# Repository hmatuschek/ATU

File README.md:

# Simple and Portable QRP Automatic Antenna Tuner
This is a first prototype for a QRP automatic antenna tuner. The final revision should provide

  - [x] Small form factor. The chassis is already set: It should fit nicely into a 10 x 10 x 3cm
        Fischer chassis.
  - [x] Tune a random wire of 10m-ish length + 1:9 UnUn on all Bands from 80m to 10m.
  - [ ] Battery powered. The chassis should contain a rechargeable battery including its charging
        circuit.
  - [ ] Using bi-stable relays the tuner should only consume power during the actual tuning.
        This increases the battery live extensively.

## Revision 0
The first prototype lacks the battery and bistable relays. Hence, it is just a platform to develop
and optimize the firmware.

## License
(c) 2020, Hannes Matuschek, DM3MAT, dm3mat (at) darc (dot) de

The firmware and hardware are published under Creative Commons License SA-BY 4.0. See LICENSE
file for details.

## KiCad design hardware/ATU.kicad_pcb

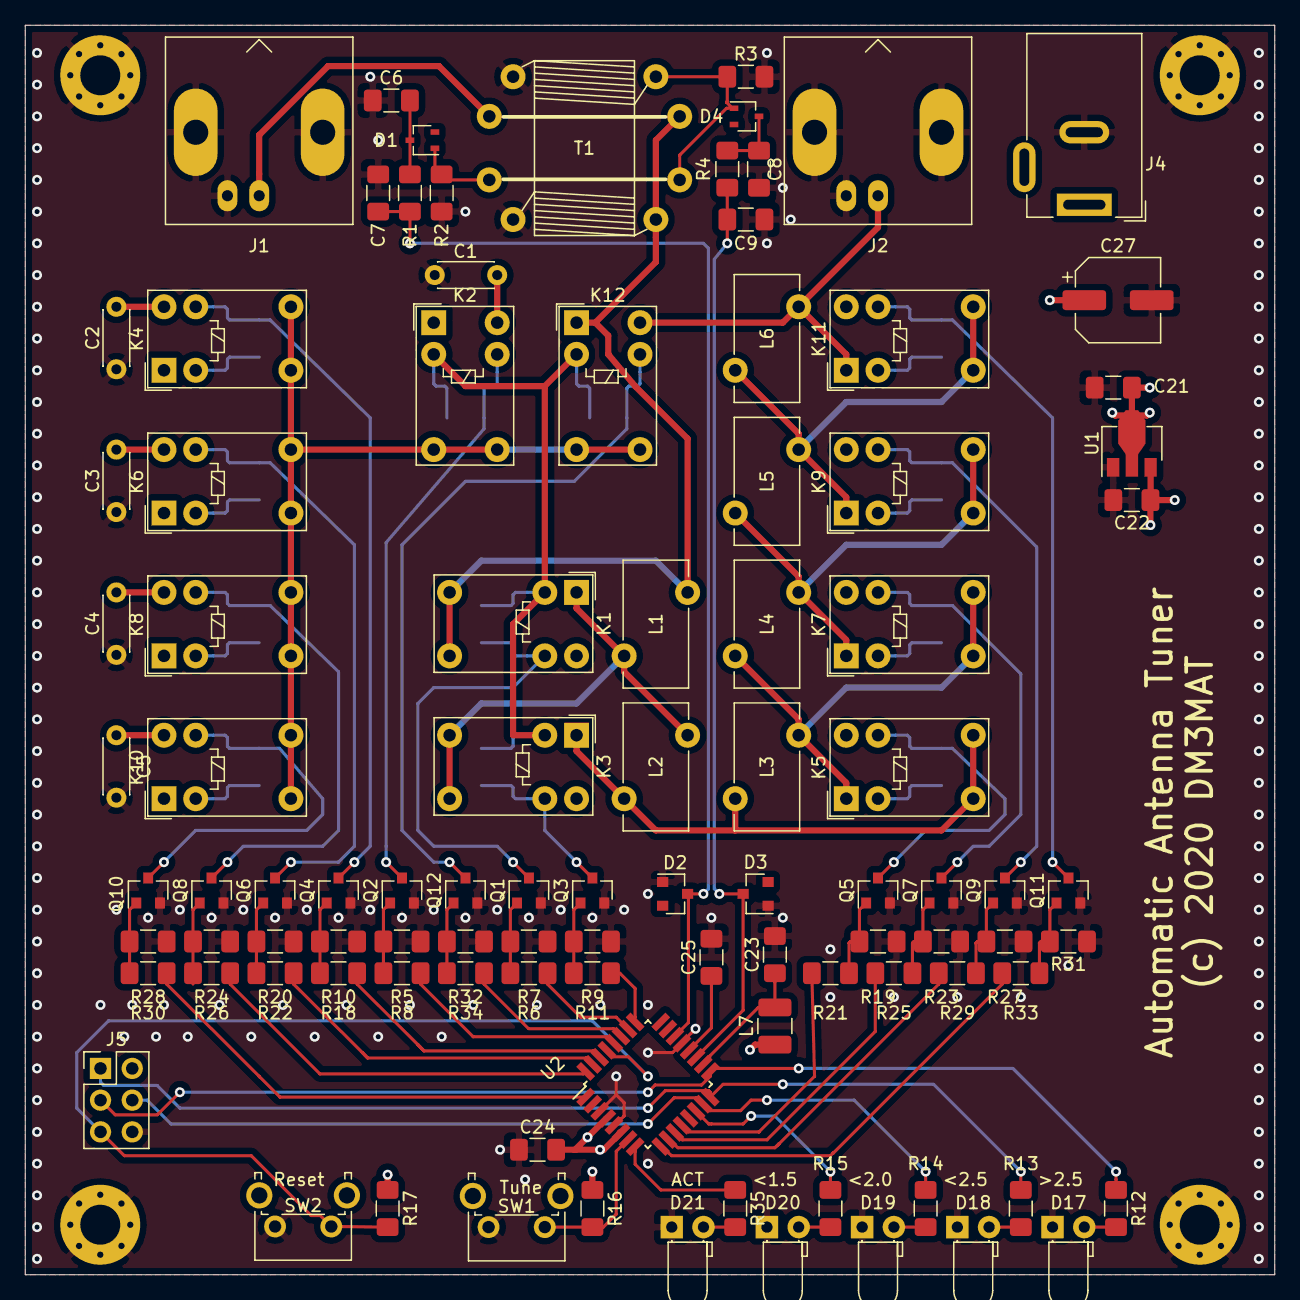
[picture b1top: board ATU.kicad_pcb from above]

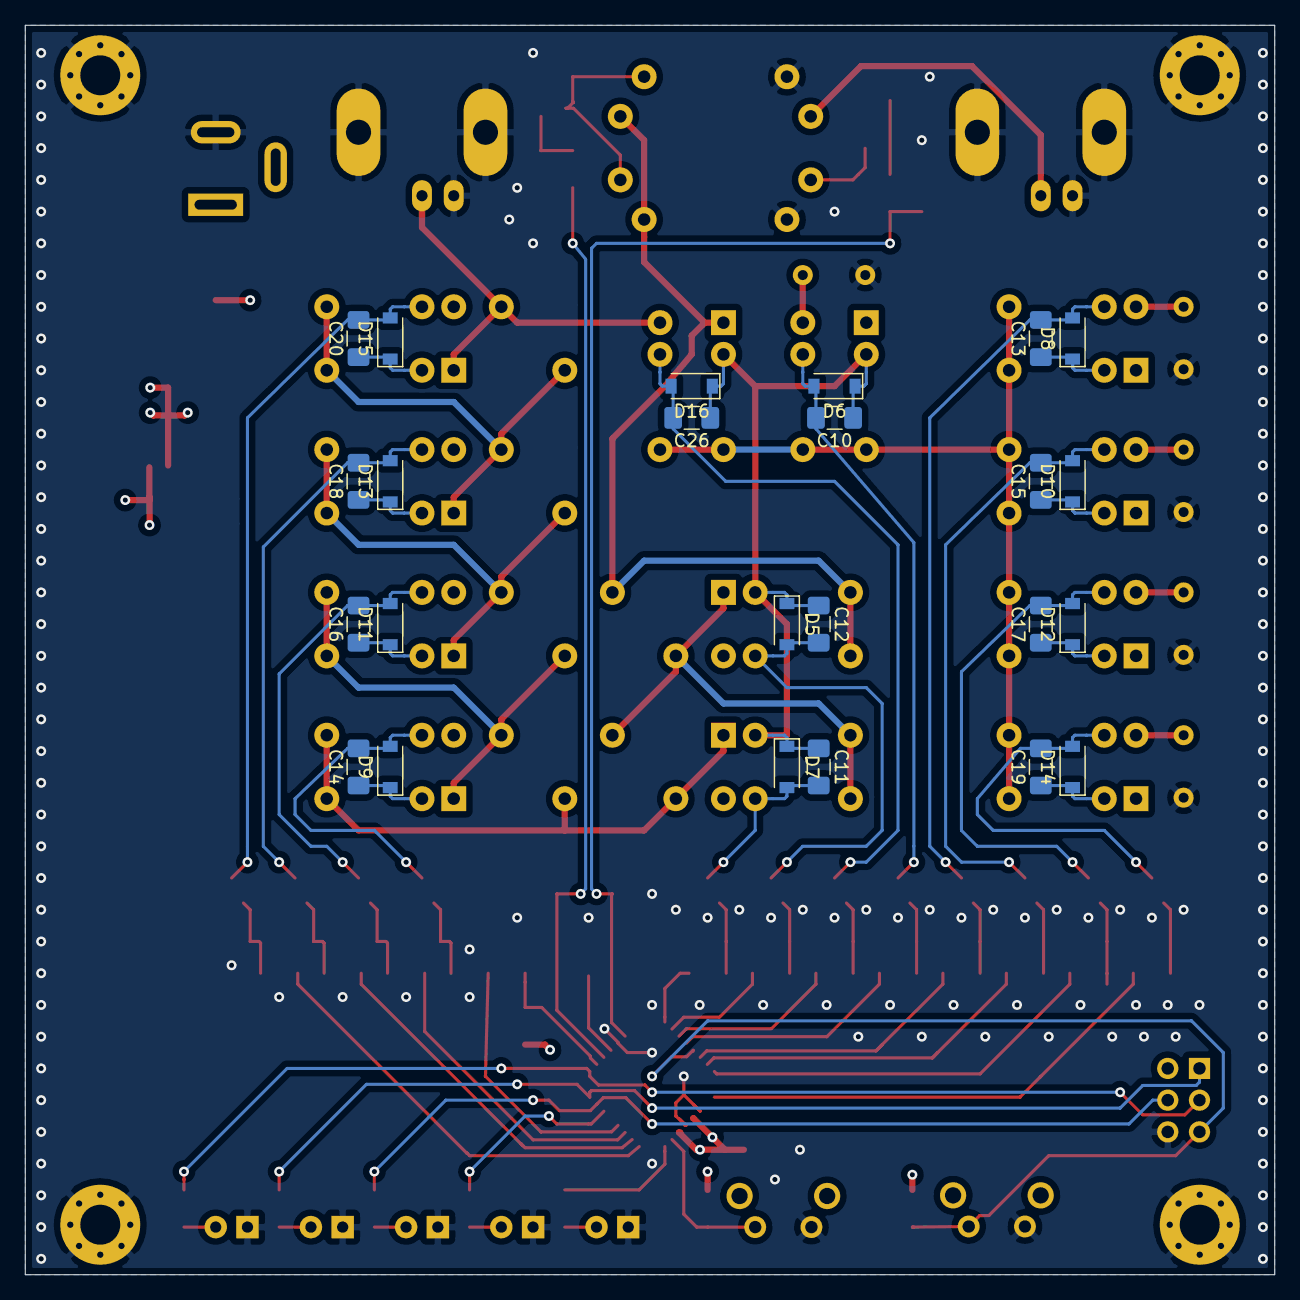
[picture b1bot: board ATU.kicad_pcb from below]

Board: 4 copper layers, 100.0 x 100.0 mm, 127 parts (24 on the bottom side), 73 nets.

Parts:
C1: 10p; C_Disc_D4.3mm_W1.9mm_P5.00mm
C2: 22p; C_Disc_D4.3mm_W1.9mm_P5.00mm
C3: 47p; C_Disc_D4.3mm_W1.9mm_P5.00mm
C4: 100p; C_Disc_D4.3mm_W1.9mm_P5.00mm
C5: 220p; C_Disc_D4.3mm_W1.9mm_P5.00mm
C6, C7, C8, C9: 10n; C_1206_3216Metric_Pad1.42x1.75mm_HandSolder
C10, C11, C12, C13, C14, C15, C16, C17, C18, C19, C20, C23, C24, C26: 100n; C_1206_3216Metric_Pad1.42x1.75mm_HandSolder
C21, C22, C25: 1u; C_1206_3216Metric_Pad1.42x1.75mm_HandSolder
C27: 100u; CP_Elec_6.3x5.8
D1, D4: BAT54W; SOT-323_SC-70
D2, D3: BZX84C5V1; D_SOT-23_ANK
D5, D6, D7, D8, D9, D10, D11, D12, D13, D14, D15, D16: 1N4148W; D_SOD-123
D17: >2.5; LED_D3.0mm_Horizontal_O1.27mm_Z2.0mm
D18: <2.5; LED_D3.0mm_Horizontal_O1.27mm_Z2.0mm
D19: <2.0; LED_D3.0mm_Horizontal_O1.27mm_Z2.0mm
D20: <1.5; LED_D3.0mm_Horizontal_O1.27mm_Z2.0mm
D21: ACT; LED_D3.0mm_Horizontal_O1.27mm_Z2.0mm
H1, H2, H3, H4: GND; MountingHole_3.2mm_M3_Pad_Via
J1: IN; BNC_Amphenol_B6252HB-NPP3G-50_Horizontal
J2: OUT; BNC_Amphenol_B6252HB-NPP3G-50_Horizontal
J4: 12-15V; BarrelJack_Wuerth_6941xx301002
J5: AVR-ISP-6; PinHeader_2x03_P2.54mm_Vertical
K1, K2, K3, K4, K5, K6, K7, K8, K9, K10, K11, K12: G5V-1; Relay_SPDT_Omron_G5V-1
L1: 0.1u; L_Toroid_Vertical_L10.0mm_W5.0mm_P5.08mm_Diagonal
L2: 0.22u; L_Toroid_Vertical_L10.0mm_W5.0mm_P5.08mm_Diagonal
L3: 0.47u; L_Toroid_Vertical_L10.0mm_W5.0mm_P5.08mm_Diagonal
L4: 1.0u; L_Toroid_Vertical_L10.0mm_W5.0mm_P5.08mm_Diagonal
L5: 2.2u; L_Toroid_Vertical_L10.0mm_W5.0mm_P5.08mm_Diagonal
L6: 4.7u; L_Toroid_Vertical_L10.0mm_W5.0mm_P5.08mm_Diagonal
L7: 100u; C_1210_3225Metric_Pad1.42x2.65mm_HandSolder
Q1, Q2, Q3, Q4, Q5, Q6, Q7, Q8, Q9, Q10, Q11, Q12: MMBT3904; SOT-23
R1, R4: 68k; R_1206_3216Metric_Pad1.42x1.75mm_HandSolder
R2, R3: 51; R_1206_3216Metric_Pad1.42x1.75mm_HandSolder
R5, R7, R9, R10, R19, R20, R23, R24, R27, R28, R31, R32: 100k; R_1206_3216Metric_Pad1.42x1.75mm_HandSolder
R6, R8, R11, R16, R17, R18, R21, R22, R25, R26, R29, R30, R33, R34: 10k; R_1206_3216Metric_Pad1.42x1.75mm_HandSolder
R12, R13, R14, R15, R35: 1.5k; R_1206_3216Metric_Pad1.42x1.75mm_HandSolder
SW1: TUNE; SW_Tactile_SPST_Angled_PTS645Vx83-2LFS
SW2: RST; SW_Tactile_SPST_Angled_PTS645Vx83-2LFS
T1: 2 x 1:10 T; Transformer_Current-Sense_Binocular
U1: MCP1703A-5002; SOT-89-3
U2: ATmega328-AU; TQFP-32_7x7mm_P0.8mm

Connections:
+5V: C22.1, C24.2, J5.2, L7.1, R16.1, R17.1, U1.3, U2.4, U2.6
+5VA: C23.1, L7.2, U2.18
+12V: C10.1, C11.1, C12.1, C13.1, C14.1, C15.1, C16.1, C17.1, C18.1, C19.1, C20.1, C21.1, C26.1, C27.1, D5.1, D6.1, D7.1, D8.1, D9.1, D10.1, D11.1, D12.1, D13.1, D14.1, D15.1, D16.1, J4.1, K1.2, K2.2, K3.2, K4.2, K5.2, K6.2, K7.2, K8.2, K9.2, K10.2, K11.2, K12.2, U1.2
ACK: R35.1, U2.8
C1+: R8.1, U2.28
C1-OC: C10.2, D6.2, K2.9, Q2.3
C2+: R18.1, U2.30
C2-OC: C13.2, D8.2, K4.9, Q4.3
C3+: R22.1, U2.31
C3-OC: C15.2, D10.2, K6.9, Q6.3
C4+: R26.1, U2.32
C4-OC: C17.2, D12.2, K8.9, Q8.3
C5+: R30.1, U2.1
C5-OC: C19.2, D14.2, K10.9, Q10.3
C-I: K2.5, K2.6, K4.5, K4.6, K6.5, K6.6, K8.5, K8.6, K10.5, K10.6, K12.5, K12.6
FWD: C7.2, D2.1, R1.2, U2.22
GND: C1.2, C2.2, C3.2, C4.2, C5.2, C6.1, C7.1, C8.2, C9.1, C21.2, C22.2, C23.2, C24.1, C25.2, C27.2, D2.2, D3.2, D17.1, D18.1, D19.1, D20.1, D21.1, H1.1, H2.1, H3.1, H4.1, J1.2, J2.2, J4.2, J5.6, Q1.2, Q2.2, Q3.2, Q4.2, Q5.2, Q6.2, Q7.2, Q8.2, Q9.2, Q10.2, Q11.2, Q12.2, R2.2, R3.2, R5.1, R7.1, R9.1, R10.1, R19.1, R20.1, R23.1, R24.1, R27.1, R28.1, R31.1, R32.1, SW1.2, SW2.2, T1.3, T1.6, U1.1, U2.3, U2.5, U2.21
IN: J1.1, T1.5
IO+: R34.1, U2.27
IO-OC: C26.2, D16.2, K12.9, Q12.3
L1+: R6.1, U2.26
L1-I: K1.5, K1.6, K12.1, L1.2, T1.2, T1.8
L1-OC: C12.2, D5.2, K1.9, Q1.3
L2+: R11.1, U2.25
L2-OC: C11.2, D7.2, K3.9, Q3.3
L3+: R21.1, U2.12
L3-OC: C14.2, D9.2, K5.9, Q5.3
L4+: R25.1, U2.11
L4-OC: C16.2, D11.2, K7.9, Q7.3
L5+: R29.1, U2.10
L5-OC: C18.2, D13.2, K9.9, Q9.3
L6+: R33.1, U2.9
L6-O: J2.1, K11.1, K12.10, L6.1
L6-OC: C20.2, D15.2, K11.9, Q11.3
MISO: J5.1, R13.1, U2.16
MOSI: J5.4, R14.1, U2.15
unnamed: C1.1, K2.10
unnamed: C2.1, K4.10
unnamed: C3.1, K6.10
unnamed: C4.1, K8.10
unnamed: C5.1, K10.10
unnamed: C6.2, D1.3, R1.1
unnamed: C8.1, D4.3, R4.1
unnamed: C25.1, U2.20
unnamed: D1.1, R2.1, T1.4
unnamed: D4.1, R3.1, T1.1, T1.7
unnamed: D17.2, R12.2
unnamed: D18.2, R13.2
unnamed: D19.2, R14.2
unnamed: D20.2, R15.2
unnamed: D21.2, R35.2
unnamed: K1.1, K3.5, K3.6, L1.1, L2.2
unnamed: K3.1, K5.5, K5.6, L2.1, L3.2
unnamed: K5.1, K7.5, K7.6, L3.1, L4.2
unnamed: K7.1, K9.5, K9.6, L4.1, L5.2
unnamed: K9.1, K11.5, K11.6, L5.1, L6.2
unnamed: Q1.1, R6.2, R7.2
unnamed: Q2.1, R5.2, R8.2
unnamed: Q3.1, R9.2, R11.2
unnamed: Q4.1, R10.2, R18.2
unnamed: Q5.1, R19.2, R21.2
unnamed: Q6.1, R20.2, R22.2
unnamed: Q7.1, R23.2, R25.2
unnamed: Q8.1, R24.2, R26.2
unnamed: Q9.1, R27.2, R29.2
unnamed: Q10.1, R28.2, R30.2
unnamed: Q11.1, R31.2, R33.2
unnamed: Q12.1, R32.2, R34.2
REV: C9.2, D3.1, R4.2, U2.19
SCK: J5.3, R12.1, U2.17
SWR3: R15.1, U2.14
TUNE: R16.2, SW1.1, U2.7
nRST: J5.5, R17.2, SW2.1, U2.29

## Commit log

2020-12-02 Init.
2020-12-02 Fixed tuner.
2020-12-18 Backup.
2020-12-19 backup
2020-12-19 Fixed FP & SYM libs.
2020-12-19 Update README.md
    Fixed typo.
2021-02-06 Cleanup tuning algorithm.
2021-02-06 Merged tuning algo from master
2021-03-28 Fixed BOM, added turns.
2021-09-19 Implemented debug build.
2022-04-02 Fixed EEPROM log.
2022-04-02 Added EEPROM log script.
2022-04-03 Fixed tuning state machine.
2022-04-03 Tag version 0.2.0
2022-04-03 Fixed minior issues.

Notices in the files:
hardware/ATU.kicad_pcb:
(c) 2020 DM3MAT
